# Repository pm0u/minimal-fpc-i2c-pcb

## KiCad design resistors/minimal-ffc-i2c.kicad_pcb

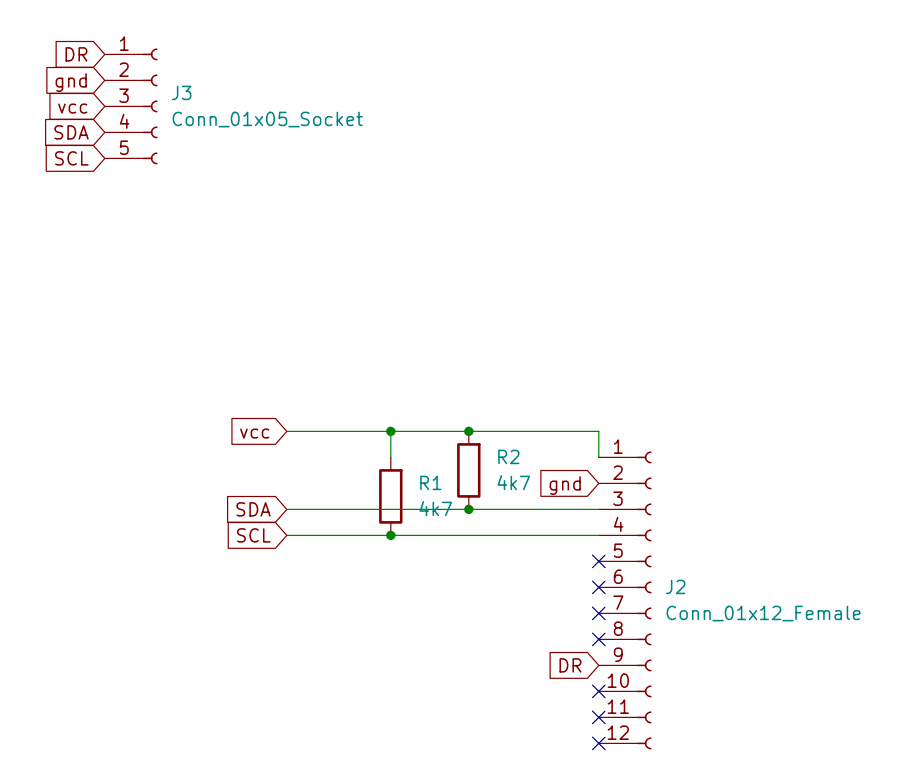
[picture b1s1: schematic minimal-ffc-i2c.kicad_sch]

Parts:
J2: Conn_01x12_Female; FPC-SMD_FPC05012-09200-.5mm-rev
J3: Conn_01x05_Socket; PinHeader_1x05_P2.54mm_Vertical
R1, R2: 4k7; R_0805_2012Metric_Pad1.20x1.40mm_HandSolder

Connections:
DR: J2.9, J3.1
SCL: J2.4, J3.5, R1.1
SDA: J2.3, J3.4, R2.1
gnd: J2.2, J3.2
vcc: J2.1, J3.3, R1.2, R2.2

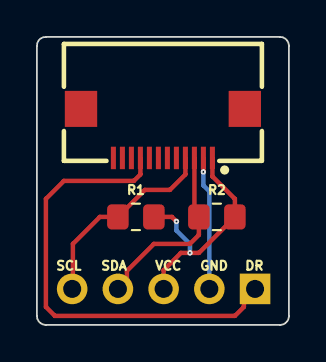
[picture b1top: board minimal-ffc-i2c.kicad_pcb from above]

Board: 2 copper layers, 14.0 x 16.0 mm, 4 parts (1 on the bottom side), 5 nets.

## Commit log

2025-01-04 rework to i2c w/ data ready, no resistors. Move files
